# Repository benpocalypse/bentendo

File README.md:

# Bentendo DMG
My take on an all in one carrier board for a Raspberry Pi Zero based handheld gaming system. 

## Backstory
I had designed this so that my 4 year old son would have an actual handheld retro system that could be kid friendly. However, after I had designed, layed out, and ordered all the parts, I only found enough free time to partially populate one of them. I hate to see all of my effort go to waste, so I'm putting this out there if anyone else is interested in trying to build one, or to fork my design and improve it.

The design of this board uses a cheap 3.2" screen that runs on the Pi's GPIO pins. I've actually tested this part, and it's working as expected. I designed the controller to use membrane pads like an actual SNES controller (or similar.) The idea was that I would just take one of those cheap SNES USB game pads, and steal the buttons/pads from them, as you can see in the picture below.

The board was designed in KiCAD, and has a BOM in it that can be directly ordered from Digikey. I've also included datasheets for all the important bits in the project as well.

Here is a 3D rendering of the board, made using FreeCAD in combination with KiCAD: 

And here is a picture of the actual board, with some components on it for a dry fit test:

And finally, a WIP case design I made in TinkerCAD:

[Here is a link to the WIP case design in Tinkercad if anyone is interested in finishing it.](https://www.tinkercad.com/things/e0lRKZJP2nW-copy-of-bentendo/editv2?sharecode=PuAttOyUiWXwXqGZIPV6nHmcgTj4fWSICqTZiEBz1Hc=)

## The Future
I still plan on coming back to this, but really wanted to put it up on GitHub so that the bits don't get lost to a computer or hard drive failure. I think I'll eventually get some time this fall to build and debug the boards I have. There may be a revision in the future...who knows...

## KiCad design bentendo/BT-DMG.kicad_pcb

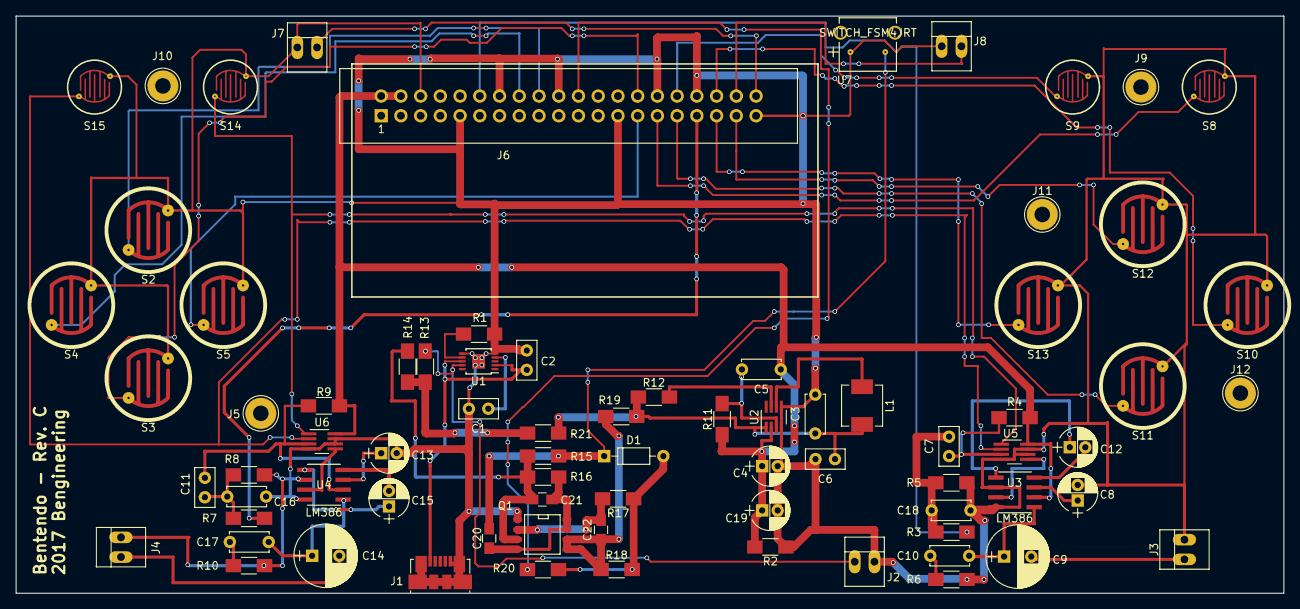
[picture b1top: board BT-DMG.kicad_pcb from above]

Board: 2 copper layers, 163.2 x 74.3 mm, 77 parts (0 on the bottom side), 52 nets.

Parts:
C1: 0.47UF; C_Disc_D5.0mm_W2.5mm_P2.50mm
C2: 4.7UF; C_Disc_D5.0mm_W2.5mm_P2.50mm
C3: 1UF; C_Disc_D5.0mm_W2.5mm_P5.00mm
C4, C19: 47UF; CP_Radial_D5.0mm_P2.00mm
C5: 220PF; C_Disc_D5.0mm_W2.5mm_P5.00mm
C6: 22UF; C_Disc_D5.0mm_W2.5mm_P2.50mm
C7, C11: 10UF; C_Disc_D5.0mm_W2.5mm_P2.50mm
C8, C12, C13, C15: 10UF; CP_Radial_D5.0mm_P2.00mm
C9, C14: 220UF; CP_Radial_D8.0mm_P3.50mm
C10, C17: 0.047UF; C_Disc_D5.0mm_W2.5mm_P5.00mm
C16, C18: 33NF; C_Disc_D5.0mm_W2.5mm_P5.00mm
C20: 1uF; C_0805_HandSoldering
C21: 0.1uF; C_0805_HandSoldering
C22: 10uF; C_0805_HandSoldering
D1: D; D_DO-35_SOD27_P7.62mm_Horizontal
J1: USB_OTG; USB_Micro-B_Molex_47346-0001
J2, J3, J4, J7, J8: CONN_01X02; PINHEAD1-2
J5, J9, J10, J11, J12: Conn_01x01; 1pin
J6: Raspberry_Pi_2_3; IDC_Header_Straight_40pins
L1: 1.5UH; L_Vishay_IHLP-2020
Q1: DUAL_MOSFET; SOIC-8-N
R1: 1.5K 1%; R_1206_HandSoldering
R2: 4.99K; R_1206_HandSoldering
R3, R7: 270R; R_1206_HandSoldering
R4, R6, R9, R10, R15: 10K; R_1206_HandSoldering
R5, R8: 127R; R_1206_HandSoldering
R11: 45.3K; R_1206_HandSoldering
R12, R13, R14, R19, R21: 0; R_1206_HandSoldering
R16, R18: 100K; R_1206_HandSoldering
R17: 300K; R_1206_HandSoldering
R20: 1K; R_1206_HandSoldering
S2, S3, S4, S5, S10, S11, S12, S13: MEMBRANE_PAD; membrane_button_small
S8, S9, S14, S15: MEMBRANE_PAD; membrane_button_tiny
U1: LTC4064; MSOP-10-1EP_3x3mm_Pitch0.5mm
U2: RT4812; SOT-23-8_Handsoldering
U3, U4: LM386; LM386MX-1&slash_NOPB
U5, U6: AD5228; TSOT-23-8_HandSoldering
U7: SWITCH_FSM4JRT; 1825027-5

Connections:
+BATT: R13.1, R14.1, R21.2
/5V_CHG: C2.1, J1.1, U1.2, U1.8
/BTN_A: J6.36, S10.2
/BTN_B: J6.31, S11.2
/BTN_X: J6.37, S12.2
/BTN_Y: J6.35, S13.2
/CHL_A: C7.1, R4.2, U5.3
/CHL_W: U3.3, U5.5
/CHR_A: C11.1, R9.2, U4.6, U6.3
/CHR_W: U4.3, U6.5
/D_DOWN: J6.28, S3.2
/D_LEFT: J6.16, S4.2
/D_RIGHT: J6.27, S5.2
/D_UP: J6.18, S2.2
/PWM0: J6.12, R3.2
/PWM1: J6.33, R7.2
/SDOWN: J6.22, R20.1
/SELECT: J6.29, S8.2
/SHLD_L: J6.40, J7.2
/SHLD_R: J6.38, J8.2
/START: J6.32, S9.2
/VOL_DN: S15.2, U5.2, U6.2
/VOL_UP: S14.2, U5.1, U6.1
GND: C1.2, C2.2, C3.2, C4.2, C6.2, C8.2, C13.2, C16.2, C18.2, C19.2, J1.5, J1.6, J2.2, J3.2, J4.2, J6.6, J6.9, J6.14, J6.20, J6.25, J6.30, J6.34, J6.39, J7.1, J8.1, Q1.1, R1.2, R2.1, R5.2, R6.2, R8.2, R10.2, S2.1, S3.1, S4.1, S5.1, S8.1, S9.1, S10.1, S11.1, S12.1, S13.1, S14.1, S15.1, U1.5, U1.6, U1.11, U2.4, U2.5, U3.2, U3.4, U4.2, U4.4, U5.4, U5.6, U5.7, U6.4, U6.6, U6.7, U7.1
unnamed: C1.1, U1.4
unnamed: C3.1, C6.1, L1.2, R12.1, R19.2, R21.1, U2.1
unnamed: C5.2, R11.2, U2.3
unnamed: C8.1, U3.7
unnamed: C9.2, J3.1
unnamed: C9.1, C10.1, U3.5
unnamed: C10.2, R6.1
unnamed: C11.2, C16.1, R7.1, R8.1
unnamed: C12.1, U3.1
unnamed: C12.2, U3.8
unnamed: C13.1, U4.7
unnamed: C14.1, C17.1, U4.5
unnamed: C14.2, J4.1
unnamed: C15.1, U4.1
unnamed: C15.2, U4.8
unnamed: C17.2, R10.1
unnamed: C7.2, C18.1, R3.1, R5.1
unnamed: C20.1, D1.1, R15.2, U7.2
unnamed: C20.2, C21.2, Q1.4, Q1.7, Q1.8, R16.2
unnamed: C21.1, Q1.3, R14.2, R15.1, R16.1
unnamed: C22.1, Q1.5, Q1.6, R18.1, R19.1
unnamed: C22.2, Q1.2, R17.2
unnamed: D1.2, R17.1, R18.2, R20.2
unnamed: J2.1, R13.2, U1.9
unnamed: L1.1, U2.6
unnamed: R1.1, U1.7
unnamed: R12.2, U2.7
VPP: C4.1, C5.1, C19.1, J6.2, J6.4, R2.2, R4.1, R9.1, R11.1, U2.2, U3.6, U5.8, U6.8

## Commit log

2018-06-05 Added content
    Added all the files I have so far, just need to fix up the Readme file after this, hopefully.
2018-06-05 Fixed Readme
    Put the images in the right spot.
2018-06-05 Fixed typo
    Oops.
2018-06-05 Another typo
    Oops again.
